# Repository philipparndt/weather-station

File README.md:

# weather-station

Weather station implemented with esphome

- [ESP32-POE](https://www.olimex.com/Products/IoT/ESP32/ESP32-POE/open-source-hardware)
- [Eltako-Windsensor-WS](https://www.amazon.de/Eltako-Windsensor-WS/dp/B0018LBFG8)
- [Temparature sensors (1-wire)](https://www.amazon.de/gp/product/B075FV3PQR)
- [DHT sensor (humidity / temperature)](https://www.amazon.de/ICQUANZX-AAM2302B-Interface-Temperature-DC3-3-5-5V/dp/B07VBVC366)
- [BH1750 Light sensor](https://www.amazon.de/dp/B07YDH737W)
- [OLED display](https://www.amazon.de/gp/product/B01MSPCZWZ)

Features:
- POE power supply
- Ethernet
- Custom MQTT messages
- Packed in a [electrical junction box](https://www.amazon.de/Kopp-347114008-Abzweigdose-Aufputz-Feuchtraum-Klemmleiste/dp/B00BGT6MK6)

# Messages

// TBD

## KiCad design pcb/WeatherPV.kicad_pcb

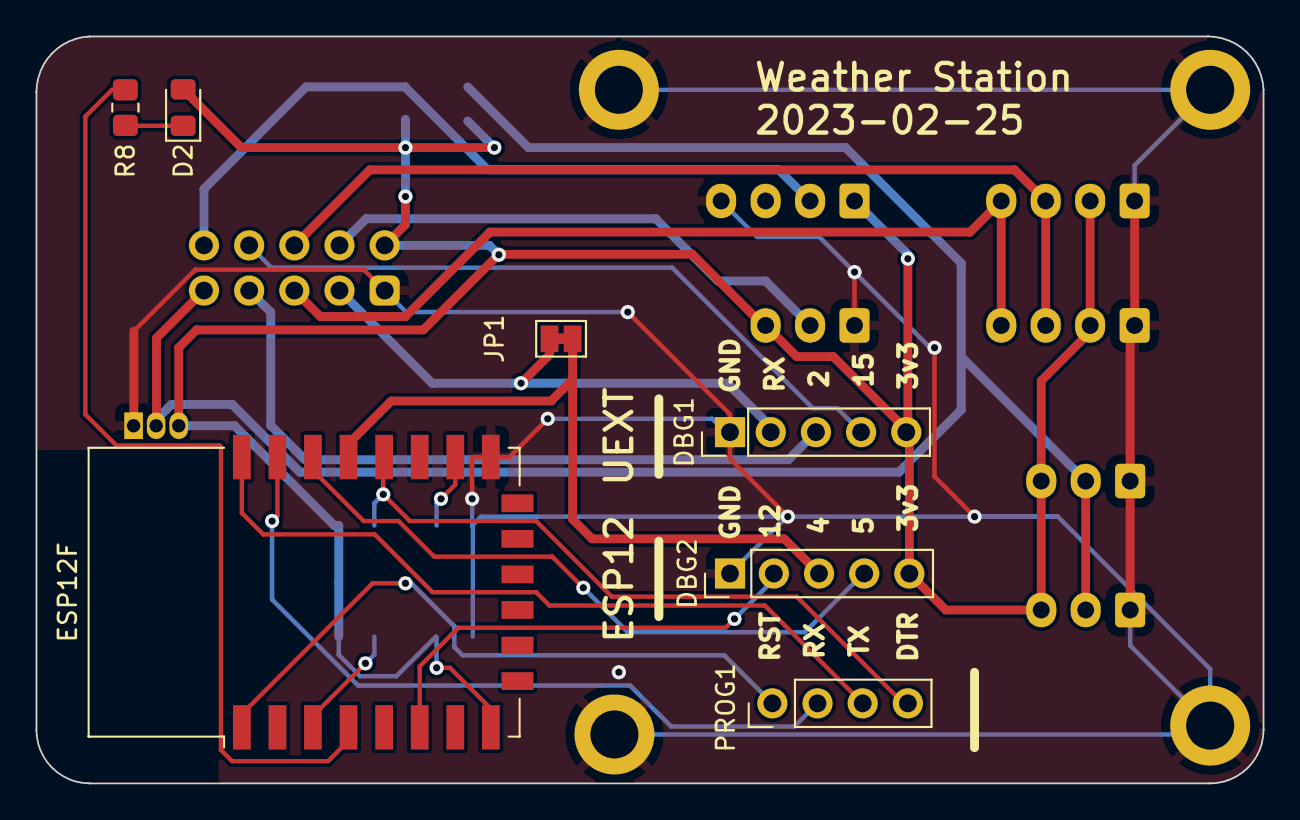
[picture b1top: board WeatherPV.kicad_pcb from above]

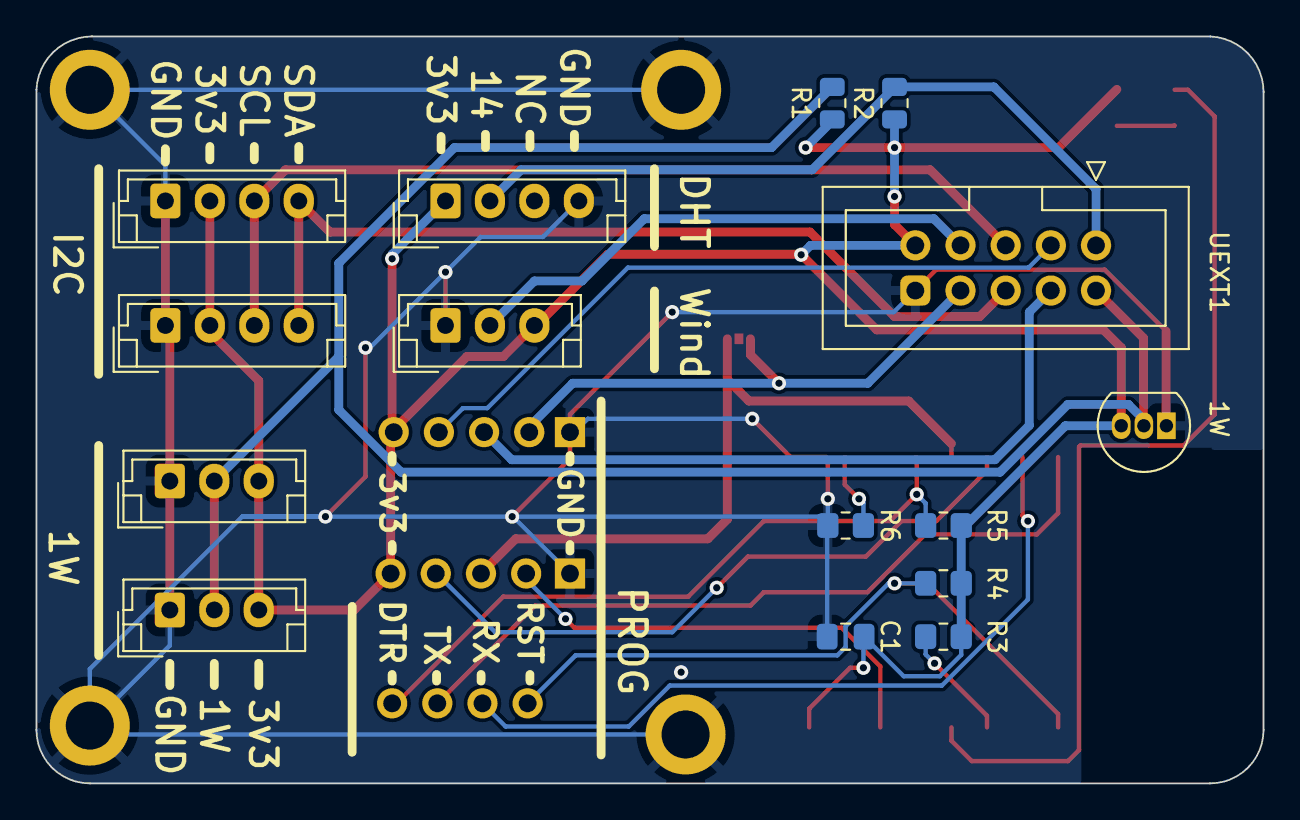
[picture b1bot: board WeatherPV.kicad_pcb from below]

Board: 2 copper layers, 69.0 x 42.0 mm, 26 parts (15 on the bottom side), 21 nets.

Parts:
1W: DS18B20; TO-92_Inline
1W1, 1W2: 1Wire; JST_EH_B3B-EH-A_1x03_P2.50mm_Vertical
C1: 100n; C_0805_2012Metric_Pad1.18x1.45mm_HandSolder
D2: LED; LED_0805_2012Metric_Pad1.15x1.40mm_HandSolder
DBG1: UEXT_DBG; PinHeader_1x05_P2.54mm_Vertical
DBG2: ESP12_DBG; PinHeader_1x05_P2.54mm_Vertical
DHT22: DHT22; JST_EH_B4B-EH-A_1x04_P2.50mm_Vertical
ESP12F: ESP-12F; ESP-12E
H5, H6, H7, H8: MountingHole_Pad; MountingHole_2.7mm_M2.5_ISO14580_Pad
I2C1, I2C2: I2C; JST_EH_B4B-EH-A_1x04_P2.50mm_Vertical
JP1: Jumper_2_Bridged; SolderJumper-2_P1.3mm_Bridged_Pad1.0x1.5mm
PROG1: ESP12_PROG; PinHeader_1x04_P2.54mm_Vertical
R1: 4k7; R_0805_2012Metric
R2: 10k; R_0805_2012Metric
R3, R4, R5, R6: 10k; R_0805_2012Metric_Pad1.20x1.40mm_HandSolder
R8: 470; R_0805_2012Metric_Pad1.20x1.40mm_HandSolder
UEXT1: UEXT_Host; IDC-Stecker_2x05_P2.54mm_Vertical
Wind1: Wind; JST_EH_B3B-EH-A_1x03_P2.50mm_Vertical

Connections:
1W: 1W.2 (DQ), 1W1.2, 1W2.2, R1.2, UEXT1.10 (~SSEL)
+3V3: 1W.3 (VDD), 1W1.3, 1W2.3, C1.1, D2.2 (A), DBG1.5, DBG2.5, DHT22.1 (VCC), ESP12F.8 (VCC), I2C1.2, I2C2.2, R1.1, R2.1, R3.1, R4.1, R5.2, UEXT1.1 (3V3), Wind1.3
ESP12_DTR: ESP12F.18 (GPIO0), PROG1.4, R5.1
ESP12_GPIO5: DBG2.4, ESP12F.20 (GPIO5)
ESP12_GPIO12: DBG2.2, ESP12F.6 (GPIO12)
ESP12_RESET: ESP12F.1 (~RST), PROG1.1, R4.2
ESP12_RX: ESP12F.21 (GPIO3/RXD), PROG1.2
ESP12_TX: ESP12F.22 (GPIO1/TXD), PROG1.3
GND: 1W.1 (GND), 1W1.1, 1W2.1, C1.2, DBG1.1, DBG2.1, DHT22.4 (GND), ESP12F.15 (GND), H5.1, H6.1, H7.1, H8.1, I2C1.1, I2C2.1, R6.2, UEXT1.2 (GND), Wind1.1
GPIO2: DBG1.3, UEXT1.8 (MOSI)
GPIO4: UEXT1.3 (TXD), Wind1.2
GPIO14: DHT22.2 (IO), R2.2, UEXT1.9 (SCK)
GPIO15: DBG1.4, UEXT1.7 (MISO)
unnamed: D2.1 (K), R8.1
unnamed: ESP12F.3 (EN), R3.2
unnamed: ESP12F.16 (GPIO15), R6.1
unnamed: ESP12F.4 (GPIO16), R8.2
RXD: DBG1.2, JP1.1 (A), UEXT1.4 (RXD)
SCL: I2C1.3, I2C2.3, UEXT1.5 (SCL)
SDA: I2C1.4, I2C2.4, UEXT1.6 (SDA)
UART_CONNECT: DBG2.3, ESP12F.19 (GPIO4), JP1.2 (B)

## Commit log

2021-08-29 initial
2021-08-29 clean-up
2021-08-29 round temperatures
2021-08-29 add support for multiple screens
2021-08-29 upload script
2021-10-25 update dht sensor
2021-10-26 fix dht
2021-10-26 disable display for production
2022-04-25 retain messages
2022-07-24 dns + hostname
2022-10-31 update mqtt broker
2023-02-17 mqtt
2023-04-06 filter invalid values
2024-01-25 update broker
2024-04-28 update network settings
2024-11-24 chore: esphome update
2025-02-27 chore(deps)
2025-02-27 chore(deps) (#1)
